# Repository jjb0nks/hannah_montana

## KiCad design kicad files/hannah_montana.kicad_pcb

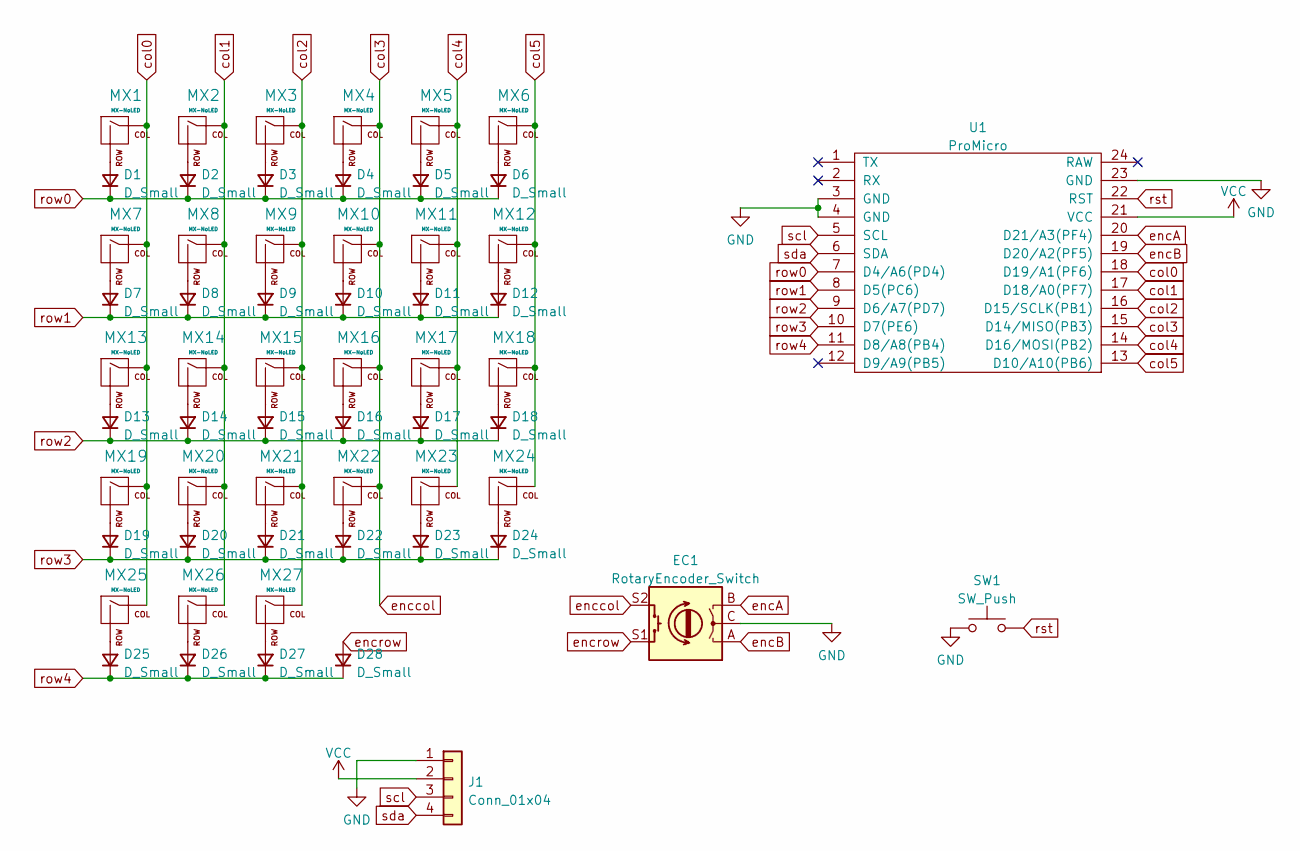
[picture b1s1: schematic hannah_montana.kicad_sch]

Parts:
D1, D2, D3, D4, D5, D6, D7, D8, D9, D10, D11, D12, D13, D14, D15, D16, D17, D18, D19, D20, D21, D22, D23, D24, D25, D26, D27, D28: D_Small; diode
EC1: RotaryEncoder_Switch; encoder
J1: Conn_01x04; oled
MX1, MX2, MX3, MX4, MX5, MX6, MX7, MX8, MX9, MX12, MX13, MX14, MX15, MX16, MX17, MX18, MX19, MX20, MX21, MX22, MX24, MX25, MX26, MX27: MX-NoLED; 1u
MX10: MX-NoLED; iso
MX11: MX-NoLED; 1.25u
MX23: MX-NoLED; 2u
SW1: SW_Push; switch
U1: ProMicro

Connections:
GND: EC1.C, J1.1, SW1.1, U1.3 (GND), U1.4 (GND), U1.23 (GND)
unnamed: D1.2 (A), MX1.2 (ROW)
unnamed: D2.2 (A), MX2.2 (ROW)
unnamed: D3.2 (A), MX3.2 (ROW)
unnamed: D4.2 (A), MX4.2 (ROW)
unnamed: D5.2 (A), MX5.2 (ROW)
unnamed: D6.2 (A), MX6.2 (ROW)
unnamed: D7.2 (A), MX7.2 (ROW)
unnamed: D8.2 (A), MX8.2 (ROW)
unnamed: D9.2 (A), MX9.2 (ROW)
unnamed: D10.2 (A), MX10.2 (ROW)
unnamed: D11.2 (A), MX11.2 (ROW)
unnamed: D12.2 (A), MX12.2 (ROW)
unnamed: D13.2 (A), MX13.2 (ROW)
unnamed: D14.2 (A), MX14.2 (ROW)
unnamed: D15.2 (A), MX15.2 (ROW)
unnamed: D16.2 (A), MX16.2 (ROW)
unnamed: D17.2 (A), MX17.2 (ROW)
unnamed: D18.2 (A), MX18.2 (ROW)
unnamed: D19.2 (A), MX19.2 (ROW)
unnamed: D20.2 (A), MX20.2 (ROW)
unnamed: D21.2 (A), MX21.2 (ROW)
unnamed: D22.2 (A), MX22.2 (ROW)
unnamed: D23.2 (A), MX23.2 (ROW)
unnamed: D24.2 (A), MX24.2 (ROW)
unnamed: D25.2 (A), MX25.2 (ROW)
unnamed: D26.2 (A), MX26.2 (ROW)
unnamed: D27.2 (A), MX27.2 (ROW)
VCC: J1.2, U1.21 (VCC)
col0: MX1.1 (COL), MX7.1 (COL), MX13.1 (COL), MX19.1 (COL), MX25.1 (COL), U1.18 (D19/A1(PF6))
col1: MX2.1 (COL), MX8.1 (COL), MX14.1 (COL), MX20.1 (COL), MX26.1 (COL), U1.17 (D18/A0(PF7))
col2: MX3.1 (COL), MX9.1 (COL), MX15.1 (COL), MX21.1 (COL), MX27.1 (COL), U1.16 (D15/SCLK(PB1))
col4: MX5.1 (COL), MX11.1 (COL), MX17.1 (COL), MX23.1 (COL), U1.14 (D16/MOSI(PB2))
col5: MX6.1 (COL), MX12.1 (COL), MX18.1 (COL), MX24.1 (COL), U1.13 (D10/A10(PB6))
encA: EC1.B, U1.20 (D21/A3(PF4))
encB: EC1.A, U1.19 (D20/A2(PF5))
enccol: EC1.S2, MX4.1 (COL), MX10.1 (COL), MX16.1 (COL), MX22.1 (COL), U1.15 (D14/MISO(PB3))
encrow: D28.2 (A), EC1.S1
row0: D1.1 (K), D2.1 (K), D3.1 (K), D4.1 (K), D5.1 (K), D6.1 (K), U1.7 (D4/A6(PD4))
row1: D7.1 (K), D8.1 (K), D9.1 (K), D10.1 (K), D11.1 (K), D12.1 (K), U1.8 (D5(PC6))
row2: D13.1 (K), D14.1 (K), D15.1 (K), D16.1 (K), D17.1 (K), D18.1 (K), U1.9 (D6/A7(PD7))
row3: D19.1 (K), D20.1 (K), D21.1 (K), D22.1 (K), D23.1 (K), D24.1 (K), U1.10 (D7(PE6))
row4: D25.1 (K), D26.1 (K), D27.1 (K), D28.1 (K), U1.11 (D8/A8(PB4))
rst: SW1.2, U1.22 (RST)
scl: J1.3, U1.5 (SCL)
sda: J1.4, U1.6 (SDA)

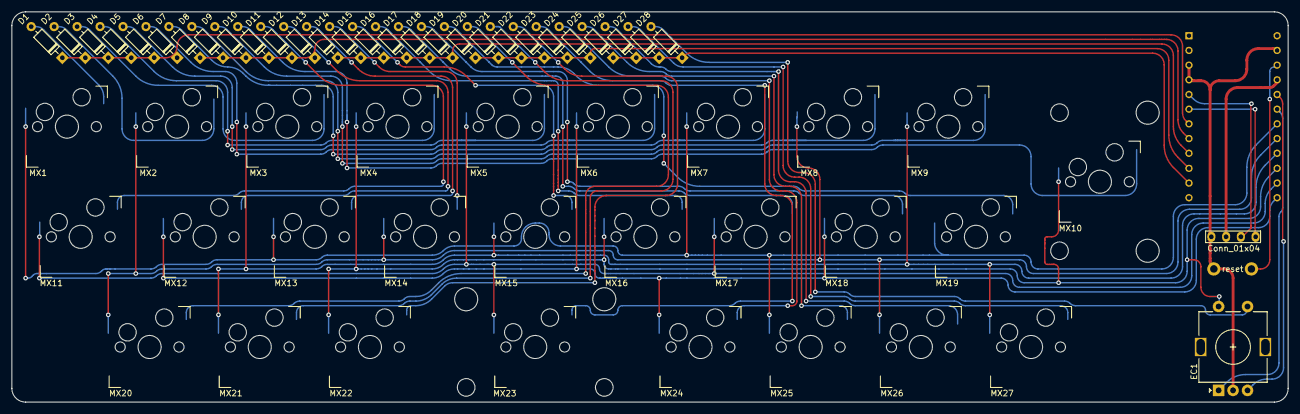
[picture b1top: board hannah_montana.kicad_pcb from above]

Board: 2 copper layers, 220.7 x 67.5 mm, 59 parts (0 on the bottom side), 46 nets.

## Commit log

2022-05-26 created kicad project
2022-05-26 add submodules
2022-05-26 added matrix +encoder to schematic
2022-05-26 finished schematic
2022-05-26 added links to important things
2022-05-26 added oled footprint
2022-05-27 modified some key footprints
2022-05-27 added more footprints
2022-05-27 assigned footprints
2022-05-27 created pcb
2022-05-27 placed key footprints
2022-05-27 placed diodes
2022-05-27 placed pro micro, oled, encoder, rst swtch
2022-05-27 created pcb outline
2022-06-01 routed and rounded everything
    i should comit more often. also the routing is terrible i hate it
2022-06-01 added gerbers
2022-06-01 created outline of copper layer thing
2022-06-01 created art file
2022-06-01 added more art, improved rounding
2022-06-01 fixed problems with routing
2022-06-01 fixed more problems with routing
2022-06-02 updated pro micro footprint
